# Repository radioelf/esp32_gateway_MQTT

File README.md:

# esp32_gateway_MQTT
PCB para Gateway ESP32, para usar con [openmqttgateway](https://docs.openmqttgateway.com/)

Creative Commons License Disclaimer

UNLESS OTHERWISE MUTUALLY AGREED TO BY THE PARTIES IN WRITING, LICENSOR OFFERS THE WORK AS-IS AND MAKES NO REPRESENTATIONS OR WARRANTIES OF ANY KIND CONCERNING THE WORK, EXPRESS, IMPLIED, STATUTORY OR OTHERWISE, INCLUDING, WITHOUT LIMITATION, WARRANTIES OF TITLE, MERCHANTIBILITY, FITNESS FOR A PARTICULAR PURPOSE, NONINFRINGEMENT, OR THE ABSENCE OF LATENT OR OTHER DEFECTS, ACCURACY, OR THE PRESENCE OF ABSENCE OF ERRORS, WHETHER OR NOT DISCOVERABLE. SOME JURISDICTIONS DO NOT ALLOW THE EXCLUSION OF IMPLIED WARRANTIES, SO SUCH EXCLUSION MAY NOT APPLY TO YOU. EXCEPT TO THE EXTENT REQUIRED BY APPLICABLE LAW, IN NO EVENT WILL LICENSOR BE LIABLE TO YOU ON ANY LEGAL THEORY FOR ANY SPECIAL, INCIDENTAL, CONSEQUENTIAL, PUNITIVE OR EXEMPLARY DAMAGES ARISING OUT OF THIS LICENSE OR THE USE OF THE WORK, EVEN IF LICENSOR HAS BEEN ADVISED OF THE POSSIBILITY OF SUCH DAMAGES.

http://creativecommons.org/licenses/by-sa/3.0/

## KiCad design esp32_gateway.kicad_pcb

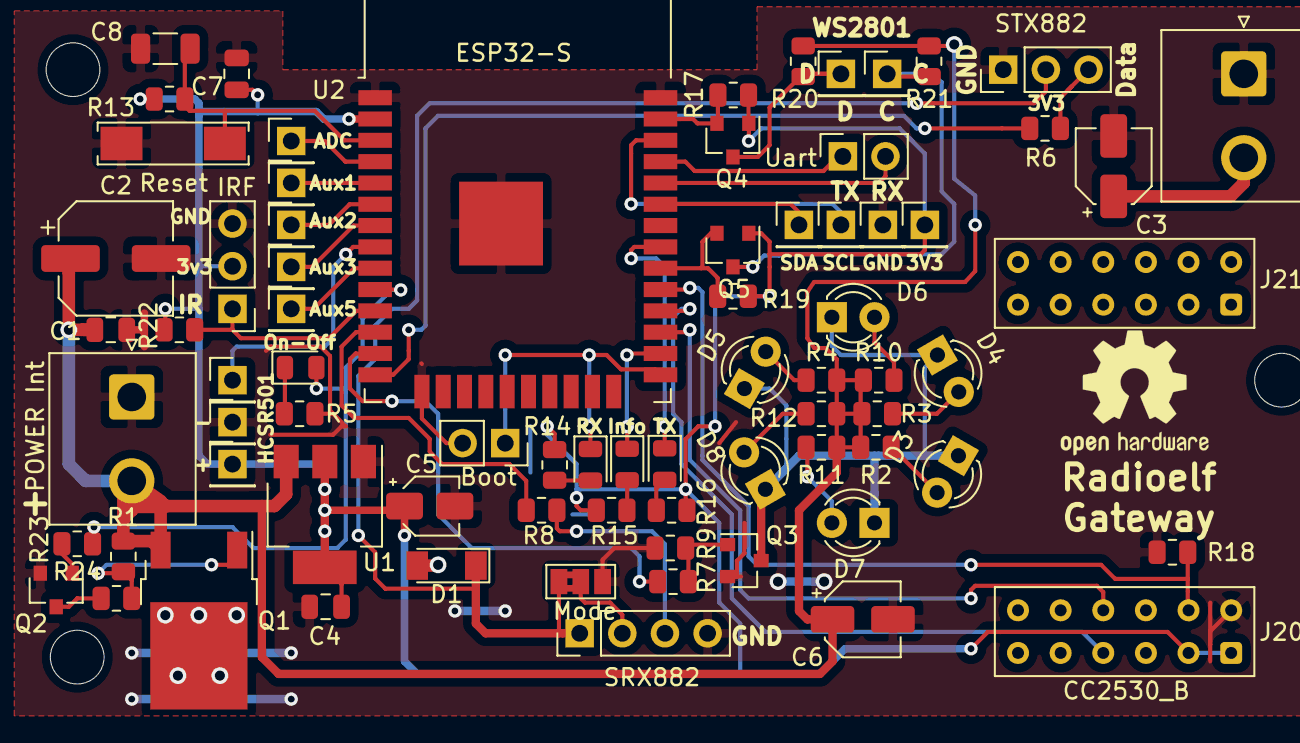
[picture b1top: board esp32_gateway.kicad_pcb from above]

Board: 2 copper layers, 75 parts (0 on the bottom side), 49 nets.

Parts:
C1, C4, C7: 100nF; C_0805_2012Metric
C2: 220uF; CP_Elec_6.3x3
C3, C6: 100uF; CP_Elec_4x3.9
C5: 22uF; CP_Elec_3x5.4
C8: 1uF; C_1206_3216Metric
D1: LL4148; D_MiniMELF
D2: white; LED_0805_2012Metric
D3, D4, D5, D6, D7, D8: TSAL6200; LED_D3.0mm_IRBlack
D9: Orange; LED_0805_2012Metric
D10: Red; LED_0805_2012Metric
D11: Green; LED_0805_2012Metric
J1: POWER Int; JST_NV_B02P-NV_1x02_P5.00mm_Vertical
J2: POWER Out; JST_NV_B02P-NV_1x02_P5.00mm_Vertical
J3, J4, J9, J11, J12, J13, J14, J15, J16, J17, J18, J19, J22, J23: Conn_01x01_Female; PinHeader_1x01_P2.54mm_Vertical
J5: Uart; PinSocket_1x02_P2.54mm_Vertical
J6: Boot; PinSocket_1x02_P2.54mm_Vertical
J7: STX882; PinHeader_1x03_P2.54mm_Vertical
J8: SRX882; PinHeader_1x04_P2.54mm_Vertical
J10: IRF; PinHeader_1x03_P2.54mm_Vertical
J20: CC2530_B; Samtec_HLE-106-02-xx-DV-TE_2x06_P2.54mm_Horizontal
J21: CC2530_A; Samtec_HLE-106-02-xx-DV-TE_2x06_P2.54mm_Horizontal
JP1: Mode; SolderJumper-3_P1.3mm_Bridged2Bar12_Pad1.0x1.5mm_NumberLabe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
Q1: DMP4051LK3; TO-252-2
Q2: BC847; SOT-23
Q3: BSS138; SOT-23
Q4, Q5: 2N7002; SOT-23
R1: 4k7; R_0805_2012Metric
R2, R3, R4, R10, R11, R12: 68; R_0805_2012Metric
R5, R7, R23: 1k; R_0805_2012Metric
R6, R8: 100; R_0805_2012Metric
R9, R13: 10K; R_0805_2012Metric
R14, R15, R16: 470; R_0805_2012Metric
R17, R18, R19, R20, R21, R24: 10k; R_0805_2012Metric
R22: 4K7; R_0805_2012Metric
SW1: Reset; SW_SPST_REED_CT05-XXXX-J1
U1: LM1117-3.3; SOT-223-3_TabPin2
U2: ESP32-S; ESP32-WROOM-32

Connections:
+3V3: C4.1, C5.1, C7.1, J9.1, J10.2, J11.1, J20.1, J20.3, Q4.1, Q5.1, R13.1, R14.2, R15.2, R16.2, R17.1, R19.1, R22.1, U1.2, U2.2
+5V: C1.1, C2.1, C6.1, J1.2, Q1.3, R1.1, R2.2, R3.2, R4.2, R10.1, R11.1, R12.1, R20.1, R21.1, U1.3
/ADC1_0: J12.1, U2.4
/AUX1: J13.1, U2.5
/AUX2: J14.1, U2.6
/AUX3: J15.1, U2.7
/AUX5: J17.1, U2.9
/EN: C8.2, R13.2, SW1.2, U2.3
/HCSR501: J16.1, U2.8
/LED_INF: D10.1, U2.26
/LED_RX: D9.1, J6.1, U2.25
/LED_TX: D11.1, U2.31
/ON-OFF: D2.2, R24.1, U2.10
/RST_CC: J20.4, R18.1, U2.29
/RXD: J5.2, U2.34
/RX_CC: J20.8, U2.27
/RX_IR: J10.1, R22.2, U2.11
/RX_RF: R6.1, U2.14
/SCL: J3.1, U2.36
/SDA: J4.1, U2.33
/TXD: J5.1, U2.35
/TX_CC: J20.7, U2.28
/TX_IR: R7.2, U2.13
/TX_RF: R8.1, U2.12
/WS2801_C: Q5.2, R19.2, U2.30
/WS2801_D: Q4.2, R17.2, U2.37
GND: C1.2, C2.2, C3.2, C4.2, C5.2, C6.2, C7.2, C8.1, J1.1, J2.1, J6.2, J7.1, J8.4, J10.3, J18.1, J19.1, J20.2, JP1.3, Q2.2, Q3.2, R5.1, R9.1, R18.2, SW1.1, U1.1, U2.1, U2.15, U2.38, U2.39
unnamed: C3.1, D1.2, J2.2, Q1.2
unnamed: D1.1, J7.2, J8.1, JP1.1
unnamed: D2.1, R5.2
unnamed: D3.1, D4.1, D5.1, D6.1, D7.1, D8.1, Q3.3
unnamed: D3.2, R2.1
unnamed: D4.2, R3.1
unnamed: D5.2, R4.1
unnamed: D6.2, R10.2
unnamed: D7.2, R11.2
unnamed: D8.2, R12.2
unnamed: D9.2, R14.1
unnamed: D10.2, R15.1
unnamed: D11.2, R16.1
unnamed: J7.3, R6.2
unnamed: J8.2, JP1.2
unnamed: J8.3, R8.2
unnamed: J22.1, Q5.3, R21.2
unnamed: J23.1, Q4.3, R20.2
unnamed: Q1.1, R1.2, R23.2
unnamed: Q2.1, R24.2
unnamed: Q2.3, R23.1
unnamed: Q3.1, R7.1, R9.2

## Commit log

2020-11-20 Gerber
    Gerber
2020-12-01 Fixed errors in RF modules connection
